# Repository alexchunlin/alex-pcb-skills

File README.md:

# alex-pcb-skills

**Pilot release: [v0.1.0-rc.1](docs/releases/v0.1.0-rc.1.md).** The completed tool changes are consolidated for
reviewed pilot-board trials. No board from this design loop has been manufactured and validated yet.

**Claude designs KiCad boards from code, routes them with a deterministic router, checks them the way an electrical
reviewer would, and packages them for the fab. Every rule in the skills points at a measured finding.**

<p align="center"><sub>A brushed-DC motor channel (DRV8874 H-bridge, TPS54620 buck, AMS1117 LDO, encoder port, 2x5 control
header, 4 layers, 50 x 40 mm), designed from a one-page brief by Claude Opus 5.5 in 71 minutes, routed by
<code>pcb route auto</code>, scored 8 / 8 / 7 by an independent reviewer agent. Nothing in it was drawn by hand.</sub></p>

## Why

An engineer's week on a board goes mostly to things a machine does better: checking every pin against the datasheet,
every rail against its current, every cap against its distance, every claim in the design log against the file. Agents
write schematics as code well (the netlist has been right on every attempt so far) and they fail in the same places every
time: a 3 A rail reaching a header pin through four 0.3 mm thermal spokes, a bulk cap fed through a chain of single vias,
a 2x10 part bought for a 2x5 footprint, a board setting lowered until DRC reads zero. ERC and DRC are blind to all of
these. `pcbcheck` turns the brief into rows that fail on them, `pcb q` measures the board so the designer and the reviewer
argue over numbers, and the reviewer's new majors become rows within a day.

Same briefs, scored by an independent reviewer agent on electrical correctness, manufacturability and documentation:

| | Rung 1, Qwiic IMU breakout | Rung 2, motor channel |
|---|---|---|
| Without the tools | 9 / 8 / 8 in 48.7 min (best of two) | not attempted |
| With the designer skill | **9 / 9 / 8 in 42.9 min** | 8 / 6 / 7 in 38.7 min (best of three) |
| With the skill and `pcb route auto` | | **8 / 8 / 7 in 71.3 min** |

The time went where the evidence said it would: three designers lost most of a rung-2 run at the DRV8874's 0.65 mm pitch,
so the next tool was a router. It routes the finished boards clean in under a minute with half the designers' vias. The
score moved; the time did not yet, because the router was allowed to make choices that are rules. That is the next item
in [`docs/ROADMAP-2026-11-01.md`](docs/ROADMAP-2026-11-01.md).

## What a run looks like

1. **Code is the source of truth.** The designer writes Zener (or SKiDL) modules, one per subsystem. The KiCad schematic
   and board are generated, and `pcb regen-check` proves the hand-placed copper survives a regeneration from a clean tree.
2. **Placement and pours by script**, with `pcblib.board` over pcbnew. Net classes, planes and keepouts come from
   `checks.json`, the declared intent: rails, currents, buses, pin maps, test points.
3. **Routing by tool.** `pcb route auto` wraps KiCadRoutingTools: engine pass, refill, dual DRC, a second pass on what is
   still open, a stitch pass. Clean means zero airwires and no new errors; the router's own "all routed" is never the
   verdict.
4. **Checks that read the brief.** `pcb check` runs the intent rows; `pcb drc` runs KiCad's DRC twice, plain and with the
   fab's rule pack, and refuses a board setup lowered below the policy.
5. **Fab package and bring-up.** Gerbers, drill, JLC BOM and CPL with sourcing fields on every part, renders, a numbered
   `BRINGUP.md` with expected readings.
6. **Independent review.** A second agent re-runs everything on a copy, re-measures every claim with `pcb q`, and scores
   against anchors. Its findings are labelled on the archived board and replayed against every tool commit.

<p align="center"><sub>The attempt-2 board with the designer's copper stripped and placement kept, then <code>pcb route auto</code>:
61 airwires to 0 in 39.5 s, 43 vias against the designer's 64. The verdict is NOT CLEAN because one thermal relief is
starved, and that one error is what the designer gets back. Pours are hidden in this view.</sub></p>

## What it catches

| Rows | Catch |
|---|---|
| `feeds`, `currents` | A pin on a wide net fed through a via, a pour neck or plane spokes below the declared current (IPC-2221, barrel plating included); a 0.2 mm track on a 3 A net |
| `decoupling`, `thermal_vias` | A bypass cap farther from its pin than the datasheet asks, on any pin type; too few vias under a thermal pad |
| `policy`, `fields` | Clearance, track, via and silk minimums lowered below the brief; parts without MPN, Manufacturer, LCSC and Datasheet |
| `calcs` | Pull-up current, buck ripple, LDO dissipation, sense scaling, each a formula with a limit that reads values from the netlist |
| pin maps, connectors, jumpers, test points | The control header against the firmware table, Qwiic pin order, address jumpers, every test point in the bring-up doc |
| dual DRC, `regen-check` | Errors that only show with the fab pack loaded; copper that does not survive regeneration |

Every row cites the finding that motivated it in [`docs/FINDINGS.md`](docs/FINDINGS.md). The replay bench
(`tools/bench/`) holds 10 boards and 41 labelled findings, including MotorGo Plink's real fab bugs; a tool commit has to
raise recall without adding a false fail. `tools/verify_all.sh` runs the integration and regression checks; see the release notes for the current validation result and prerequisites.

<p align="center"><sub>Rung 1, a Qwiic LSM6DS3TR-C breakout (Sonnet 5.5 with the skill, 9 / 9 / 8), and rung 2, the motor channel
(Opus 5.5 with the skill and the router, 8 / 8 / 7). Both are in <code>examples/</code> with their configs, reviews and labels.</sub></p>

## Where it is

- The sensor breakout received reviewer scores of 9 on electrical with minors only; it has not been physically validated. The
  named risk for a new part is sourcing: the one blocker in rung 2 was an LCSC part that did not match its footprint,
  and the row for that is next.
- The motor channel works on paper and would be a rev A with errata: the reviewer's three majors are a header pin on
  plane spokes, a bulk cap on a via chain, and no copper under the LDO. All three are labelled and all three are the
  router's choices, which the staged router removes.
- Nothing from the loop has been built yet. Every score is reviewer-measured. Ordering the two best boards is the
  cheapest calibration available and is spike [#3](https://github.com/alexchunlin/alex-pcb-skills/issues/3).

## Where it is going

- **Staged routing** that keeps signals off the planes and wide nets with the layout script, generated `feeds` rows for
  every pin of a wide net, and the datasheet rules moved from the model's thinking into `pcblib` helpers. Then rung-2
  attempt 3, with the target of 8 / 8 / 7 or better under 40 minutes.
- **Rung 3**: re-derive the MotorGo Plink (four channels, ESP32, IMU, USB) from a brief written from its README, with one
  sub-agent per schematic sheet. **Rung 4**: Pace Racer's 48 V inverter sheet.
- **Five spikes, run and merged** (`docs/spikes/`, issues #1 to #5), each with a hypothesis, a null, a cost, a
  literature review and an Opus agent that ran it in a worktree. What paid: a field solve of the declared currents on
  the real copper that passes a pour-fed board where the track-width row fails every pad and found a 3 A via pair nobody
  had labelled (#3); a mutation bench that plants six bug kinds and shows the boards' own checks catch 16 of 21, with
  every miss a missing config row (#3); a placement prior mined from 72 public boards that doubles the router's clean
  rate, 33 of 50 against 17 of 50 (#2); a generated pogo jig and bring-up script waiting on a board order (#3). What
  lost, by a number: a learned placement surrogate against plain wirelength (#1), agent-drawn routing corridors (#4),
  reference-circuit statistics and commit mining (#2). Pooling that prior by component class gives a new part one:
  39 of 50 with the part held out, against 17 uniform, though KRT's own decap cost ties it at 37 (#5).
- **A robot design acceleration toolkit.** This repo, [`alex-3d-skills`](https://github.com/alexchunlin/alex-3d-skills)
  (printed assemblies checked in headless Blender) and Harnessy (wire harnesses with design rules and a BOM) are three
  views of one machine: the board's connectors are the harness's endpoints, the harness's lengths come from the
  assembly, and the assembly's mounting holes and keepouts come from the board. The plan is one brief in, a checked
  board, harness and enclosure out, with the same loop, the same review protocol and the same replay bench behind each.

## Layout of the repo

| Path | What |
|---|---|
| `skills/kicad-design/` | Designer skill: the `pcb` wrapper (`erc`, dual `drc`, `check`, `q`, `route`, `fab`, `regen-check`, `schfix`, `py`, Diode passthrough), `pcblib.board` over pcbnew, `pcbcheck` with `checks.json`, reference docs, project template |
| `skills/pcb-design-review/` | Reviewer skill: check-first protocol, rubric with anchors, evidence checklist |
| `examples/` | The reviewed rung-1 and rung-2 attempts (configs, boards, reviews, labels) and MotorGo Plink before and after its rework |
| `tools/verify_all.sh` | Re-proves everything (`--changed [BASE]` runs only what a change affects, `--dry-run` prints the plan) |
| `tools/bench/` | Replay bench (`replay.py`, `labels.json`) and the route bench (`route_bench.py`, `results/route.jsonl`) |
| `tools/readme/` | `make_images.sh` rebuilds the images above from the archived boards |
| `bench/design/` | Design-bench briefs (rung 1 Qwiic IMU, rung 2 motor channel) and the review protocol |
| `docs/` | `GAMEPLAN.md`, `ROADMAP-2026-11-01.md`, `FINDINGS.md` (the evidence log), `STATUS.md`, `SURVEY-2026-10-31.md`, session handoffs, upstream issue drafts |

## Requirements

KiCad 10.0.1 at `/Applications/KiCad/KiCad.app` (kicad-cli and the bundled Python with `pcbnew`), Diode `pcb` 0.4.97
at `~/.local/bin/pcb` for the Zener front end, kicad-druid at `/tmp/pcb-ref/kicad-druid` (`KICAD_DRUID`) for the fab
rule packs, python3. No pip dependencies for the tools; `.venv` holds SKiDL for the fallback path. `pcb route auto` needs
KiCadRoutingTools under `/tmp/pcb-ref/` (the six-line install is in `tools/bench/README.md`). Only tested on macOS.

## Install

```sh
git clone https://github.com/alexchunlin/alex-pcb-skills.git && cd alex-pcb-skills
git checkout v0.1.0-rc.1
mkdir -p ~/.claude/skills
ln -s "$PWD/skills/kicad-design" ~/.claude/skills/kicad-design              # the designer skill
ln -s "$PWD/skills/pcb-design-review" ~/.claude/skills/pcb-design-review    # the reviewer skill
```

## Quick use

```sh
S=~/code-stuff/alex-pcb-skills/skills/kicad-design/scripts
$S/pcb drc layout/x/x.kicad_pcb --pack jlcpcb        # plain and packed DRC, sentinel, pack floored to the board setup
$S/pcb check layout/x/x.kicad_pcb checks.json        # intent rows; undeclared rails, connectors, jumpers, test points fail
$S/pcb q layout/x/x.kicad_pcb decoupling             # one measurement (pcb q alone lists them)
$S/pcb route auto layout/x/x.kicad_pcb --pack jlcpcb # route what is unrouted, dual DRC, exit 1 unless clean
$S/pcb fab layout/x/x.kicad_pcb --out fab            # gerbers, drill, JLC BOM and CPL, renders, fab.json
$S/pcb regen-check . --cmd tools/regen.sh --board layout/x/x.kicad_pcb --generated layout fab
$S/pcb schfix layout/x/x.kicad_sch                   # after pcb apply schematic
$S/pcb py tools/layout_board.py layout/x/x.kicad_pcb # a pcblib layout script
sh tools/verify_all.sh --changed --dry-run           # what this change affects
python3 -I tools/bench/replay.py                     # the replay bench on HEAD
```

Then give Claude Code a brief like `bench/design/rung2-motor-channel/BRIEF.md` and ask for a board; ask a second session
to review it with the `pcb-design-review` skill.

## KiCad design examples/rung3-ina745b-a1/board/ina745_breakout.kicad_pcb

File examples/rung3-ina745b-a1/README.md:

# INA745B Power Monitor Breakout

Measures current, bus voltage, power, energy and charge on a rail up to 40 V, over I2C, with the shunt inside the chip. Bolt the rail to two M4 terminals, plug in Qwiic, read the numbers.
40 x 25.4 mm, four M2.5 holes. Open hardware, source in Zener and Python.

**Rated 25 A continuous at 40 C ambient in still air, 40 V.** That is this board's calculation, not the chip's 35 A headline; see DESIGN_LOG.md section 2. 33 mV drop at 25 A.
The rating is calculated, not yet measured on a built board.

| Spec | Value |
|---|---|
| Sensor | TI INA745B, 16-bit, 1.2 mA/LSB, 3.125 mV/LSB, full scale +/-39.32 A |
| Accuracy | gain +/-1.25 %, offset +/-62.5 mA max (B grade) |
| Bus | -0.1 to 40 V, high side or low side |
| Logic supply | VIN 3.3 to 5.5 V on the header, or 3.3 V on Qwiic |
| I2C | 0x40 default, 100 kHz; up to 2.94 MHz in the chip |

## Pinout
| Header J3 | Name | Function |
|---|---|---|
| 1 | VIN | 3.3 to 5.5 V in, through a diode and a 3.3 V regulator |
| 2 | 3V3 | Logic rail, same copper as Qwiic 3V3 |
| 3 | GND | Logic ground. **Must be common with the measured rail's return** |
| 4 | SCL | I2C clock |
| 5 | SDA | I2C data |
| 6 | ALERT | Open drain, active low, 10 k to 3V3. Do not pull above 3.6 V |

J1, J2: Qwiic / Stemma QT, 1 GND, 2 3V3, 3 SDA, 4 SCL. J4 IS+, J5 IS-: M4 screw terminals. TP1 GND, TP2 3V3, TP3 VBUS wire pad.

## I2C address
| JP4 (A1) | JP3 (A0) | Address |
|---|---|---|
| G | G | 0x40 (shipped) |
| G | V | 0x41 |
| V | G | 0x44 |
| V | V | 0x45 |
To move a strap, cut the link to G and bridge to V. Never leave a jumper open. A wire to SCL gives more addresses (TI table 6-2); SDA needs a 100 ns hold your host may not give.

## Jumpers
JP1: closed, VBUS senses IS+ (high side). Low side: cut it and wire your rail to TP3. JP2: cut both links to drop the 10 k pull-ups. JP5: cut to turn off the power LED.

## Wiring
High side: supply + to J4, load to J5, supply - to GND. Low side: load return to J4, J5 to supply -, cut JP1, supply + to TP3, GND to the same return as J5.
Use M4 ring lugs and 10 AWG (5 mm2) wire at 25 A. Keep logic ground connected whenever the board is powered (TI 8.3).
5 V hosts: SDA and SCL tolerate 5.5 V, but they idle at 3.3 V, so a host needing 3.5 V for a high needs a level shifter.
10 k pull-ups meet 400 kHz only to 35 pF. At 400 kHz, add a stronger host pull-up or run 100 kHz.

## First read
Register 0x3E reads 0x5449. BRINGUP.md has the full sequence with expected values.

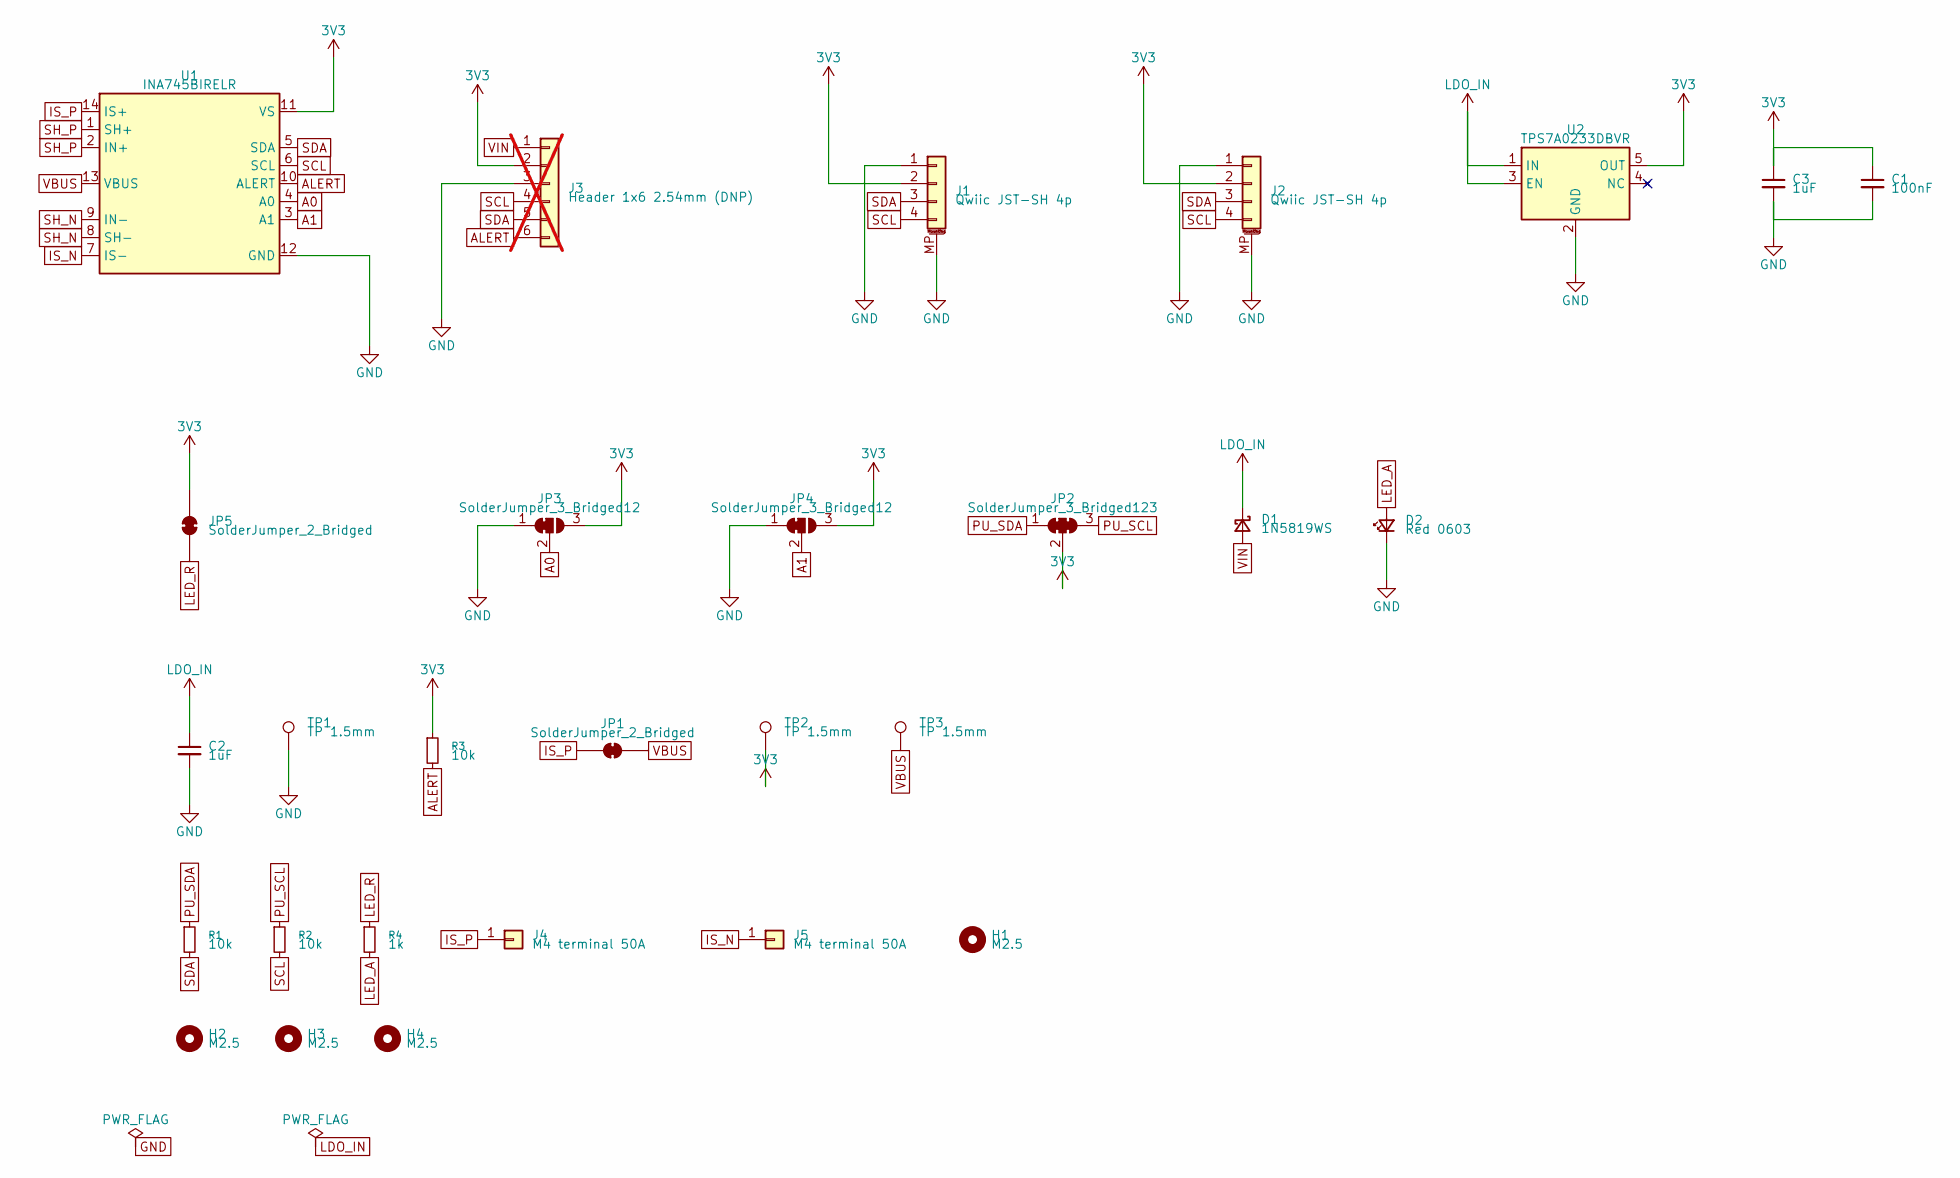
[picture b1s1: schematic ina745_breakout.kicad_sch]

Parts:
C1: 100nF; C_0402_1005Metric_NoSilk; MPN CL05B104KO5NNNC; LCSC C1525
C2, C3: 1uF; C_0603_1608Metric; MPN CL10A105KB8NNNC; LCSC C15849
D1: 1N5819WS; D_SOD-323; MPN 1N5819WS; LCSC C191023
D2: Red 0603; LED_0603_1608Metric; MPN KT-0603R; LCSC C2286
H1, H2, H3, H4: M2.5; MountingHole_2.7mm_M2.5_Head4.7
J1, J2: Qwiic JST-SH 4p; JST_SH_SM04B-SRSS-TB_1x04-1MP_P1.00mm_Horizontal; MPN SM04B-SRSS-TB(LF)(SN); LCSC C160404
J3: Header 1x6 2.54mm (DNP); PinHeader_1x06_P2.54mm_Vertical; MPN PZ254V-11-06P; LCSC C492405; not fitted
J4, J5: M4 terminal 50A; XFCN_T44008_M4; MPN T44008; LCSC C481445
JP1: SolderJumper_2_Bridged; SolderJumper-2_P1.6mm_Bridged12_Pad1.0x1.5mm
JP2: SolderJumper_3_Bridged123; SolderJumper-3_P1.3mm_Bridged123_Pad1.0x1.5mm
JP3, JP4: SolderJumper_3_Bridged12; SolderJumper-3_P1.3mm_Bridged12_Pad1.0x1.5mm
JP5: SolderJumper_2_Bridged; SolderJumper-2_P1.3mm_Bridged12_Pad1.0x1.5mm
R1, R2, R3: 10k; R_0603_1608Metric; MPN 0603WAF1002T5E; LCSC C25804
R4: 1k; R_0603_1608Metric; MPN 0603WAF1001T5E; LCSC C21190
TP1, TP2: TP 1.5mm; TestPoint_Pad_D1.5mm_Ring1.0
TP3: TP 1.5mm; TestPoint_THTPad_D2.0mm_Drill1.0mm
U1: INA745BIRELR; VQFN-14_REL0014A_3x5mm_P0.6mm; MPN INA745BIRELR; LCSC C35213810
U2: TPS7A0233DBVR; SOT-23-5; MPN TPS7A0233DBVR; LCSC C5142805

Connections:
3V3: C1.1, C3.1, J1.2, J2.2, J3.2, JP2.2 (C), JP3.3 (B), JP4.3 (B), JP5.1 (A), R3.1, TP2.1, U1.11 (VS), U2.5 (OUT)
A0: JP3.2 (C), U1.4 (A0)
A1: JP4.2 (C), U1.3 (A1)
ALERT: J3.6, R3.2, U1.10 (ALERT)
GND: C1.2, C2.2, C3.2, D2.1 (K), J1.1, J1.MP (MountPin), J2.1, J2.MP (MountPin), J3.3, JP3.1 (A), JP4.1 (A), TP1.1, U1.12 (GND), U2.2 (GND)
IS_N: J5.1, U1.7 (IS-)
IS_P: J4.1, JP1.1 (A), U1.14 (IS+)
LDO_IN: C2.1, D1.1 (K), U2.1 (IN), U2.3 (EN)
LED_A: D2.2 (A), R4.2
LED_R: JP5.2 (B), R4.1
PU_SCL: JP2.3 (B), R2.1
PU_SDA: JP2.1 (A), R1.1
SCL: J1.4, J2.4, J3.4, R2.2, U1.6 (SCL)
SDA: J1.3, J2.3, J3.5, R1.2, U1.5 (SDA)
SH_N: U1.8 (SH-), U1.9 (IN-)
SH_P: U1.1 (SH+), U1.2 (IN+)
VBUS: JP1.2 (B), TP3.1, U1.13 (VBUS)
VIN: D1.2 (A), J3.1
power.U2.NC_U_NC: U2.4 (NC)

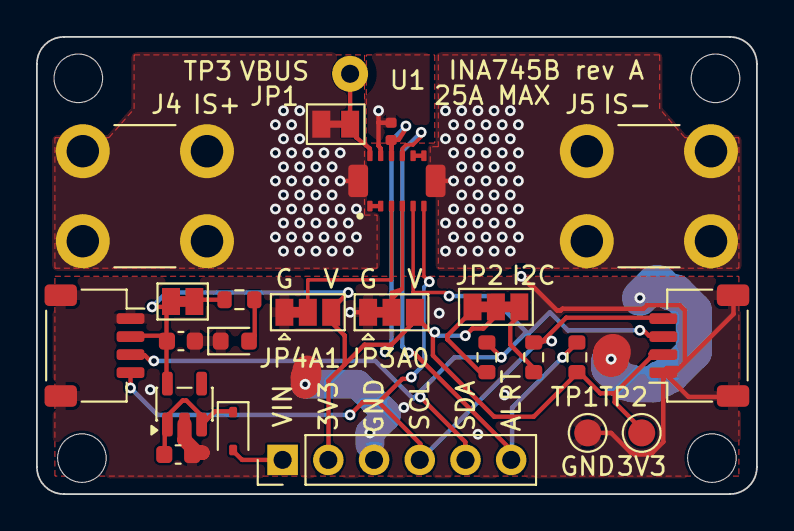
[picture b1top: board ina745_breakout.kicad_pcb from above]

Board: 4 copper layers, 40.0 x 25.4 mm, 28 parts (0 on the bottom side), 18 nets.

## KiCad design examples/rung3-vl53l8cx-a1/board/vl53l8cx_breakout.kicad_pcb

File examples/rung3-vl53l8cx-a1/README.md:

# VL53L8CX 8 x 8 Time-of-Flight Breakout, Qwiic

64-zone distance sensing to 4 m with a 45 x 45 degree field of view, up to 60 Hz. Plug into any 3.3 V Qwiic / STEMMA QT host. The ST VL53L8CX runs on 1.8 V logic and three supplies; this board makes the 1.8 V, sequences it the way the datasheet asks, and level-shifts all eight signal lines.

25.4 x 17.8 mm, two M2.5 holes, 4 layers, open hardware.

## Pinout: J3, 0.1 inch

| Pin | Name | Dir | Function |
|---|---|---|---|
| 1 | VIN | in | 3.3 to 5 V, to the on-board 3.3 V regulator |
| 2 | 3V3 | in/out | sensor rail, same net as Qwiic 3V3, 170 mA max load from this board |
| 3 | GND | | |
| 4 | MISO | out | SPI only, after bridging JP5 |
| 5 | SCL | in | I2C clock, SPI MCLK. 3.3 V level |
| 6 | SDA | in/out | I2C data, SPI MOSI. 3.3 V level |
| 7 | NCS | in | SPI chip select |
| 8 | RST | in | high pulse resets the I2C interface only. Leave open if unused. Full sensor reset is a power cycle (DS14161 Table 3 note) |
| 9 | LPN | in | low disables I2C in low-power mode. Open = enabled |
| 10 | INT | out | open-drain interrupt with a 10k pull-up to 3.3 V |

All logic on J3 and Qwiic is 3.3 V. Inputs tolerate 5 V, but a 5 V host will read SDA and INT high at only 3.3 V, so use a 3.3 V host. VIN is the only pin meant for 5 V. SYNC is on back pad TP4, 3.3 V side, with no pull-up on that side.

Qwiic J1 and J2: 1 GND, 2 3V3, 3 SDA, 4 SCL.

## I2C address

**0x29** (7-bit), 0x52 in ST's 8-bit notation. No strap: change it in software, using LPN to keep other sensors quiet. Host-side pull-ups are 10k, through JP1 on the top by J2: cut it once to remove both on a long chain. This board guarantees 400 kHz with 10k; 1 MHz needs stronger host pull-ups.

## Power

Two sources share the 3V3 rail: Qwiic 3V3, and VIN through the regulator and an ideal diode. Either or both are fine. VIN cannot be back-fed from Qwiic. With VIN on, this board powers the Qwiic connectors, so a host that is switched off on the same cable gets power on its 3V3 rail: disconnect it. The LED shows the rail; cut JP2 on the back to turn it off. Typical sensor power 215 mW while ranging.

## Cover glass

The board ships with ST's protective liner on the sensor: **peel it off before use**. If you put the board behind a window, the opening must be at least as wide as the 57.9 x 57.9 degree collector cones (DS14161 sect 2.2, Fig 28), and the glass affects crosstalk: see ST AN5897. The exclusion zone is on layer `User.1` of the KiCad board.

## I2C to SPI

Move JP3 and JP4 to pads 2-3, bridge JP5, power cycle. `BRINGUP.md` has the steps.

## Software

ST's VL53L8CX ULD driver (STSW-IMG040); user manual UM3109. Rev A has not been built or tested.

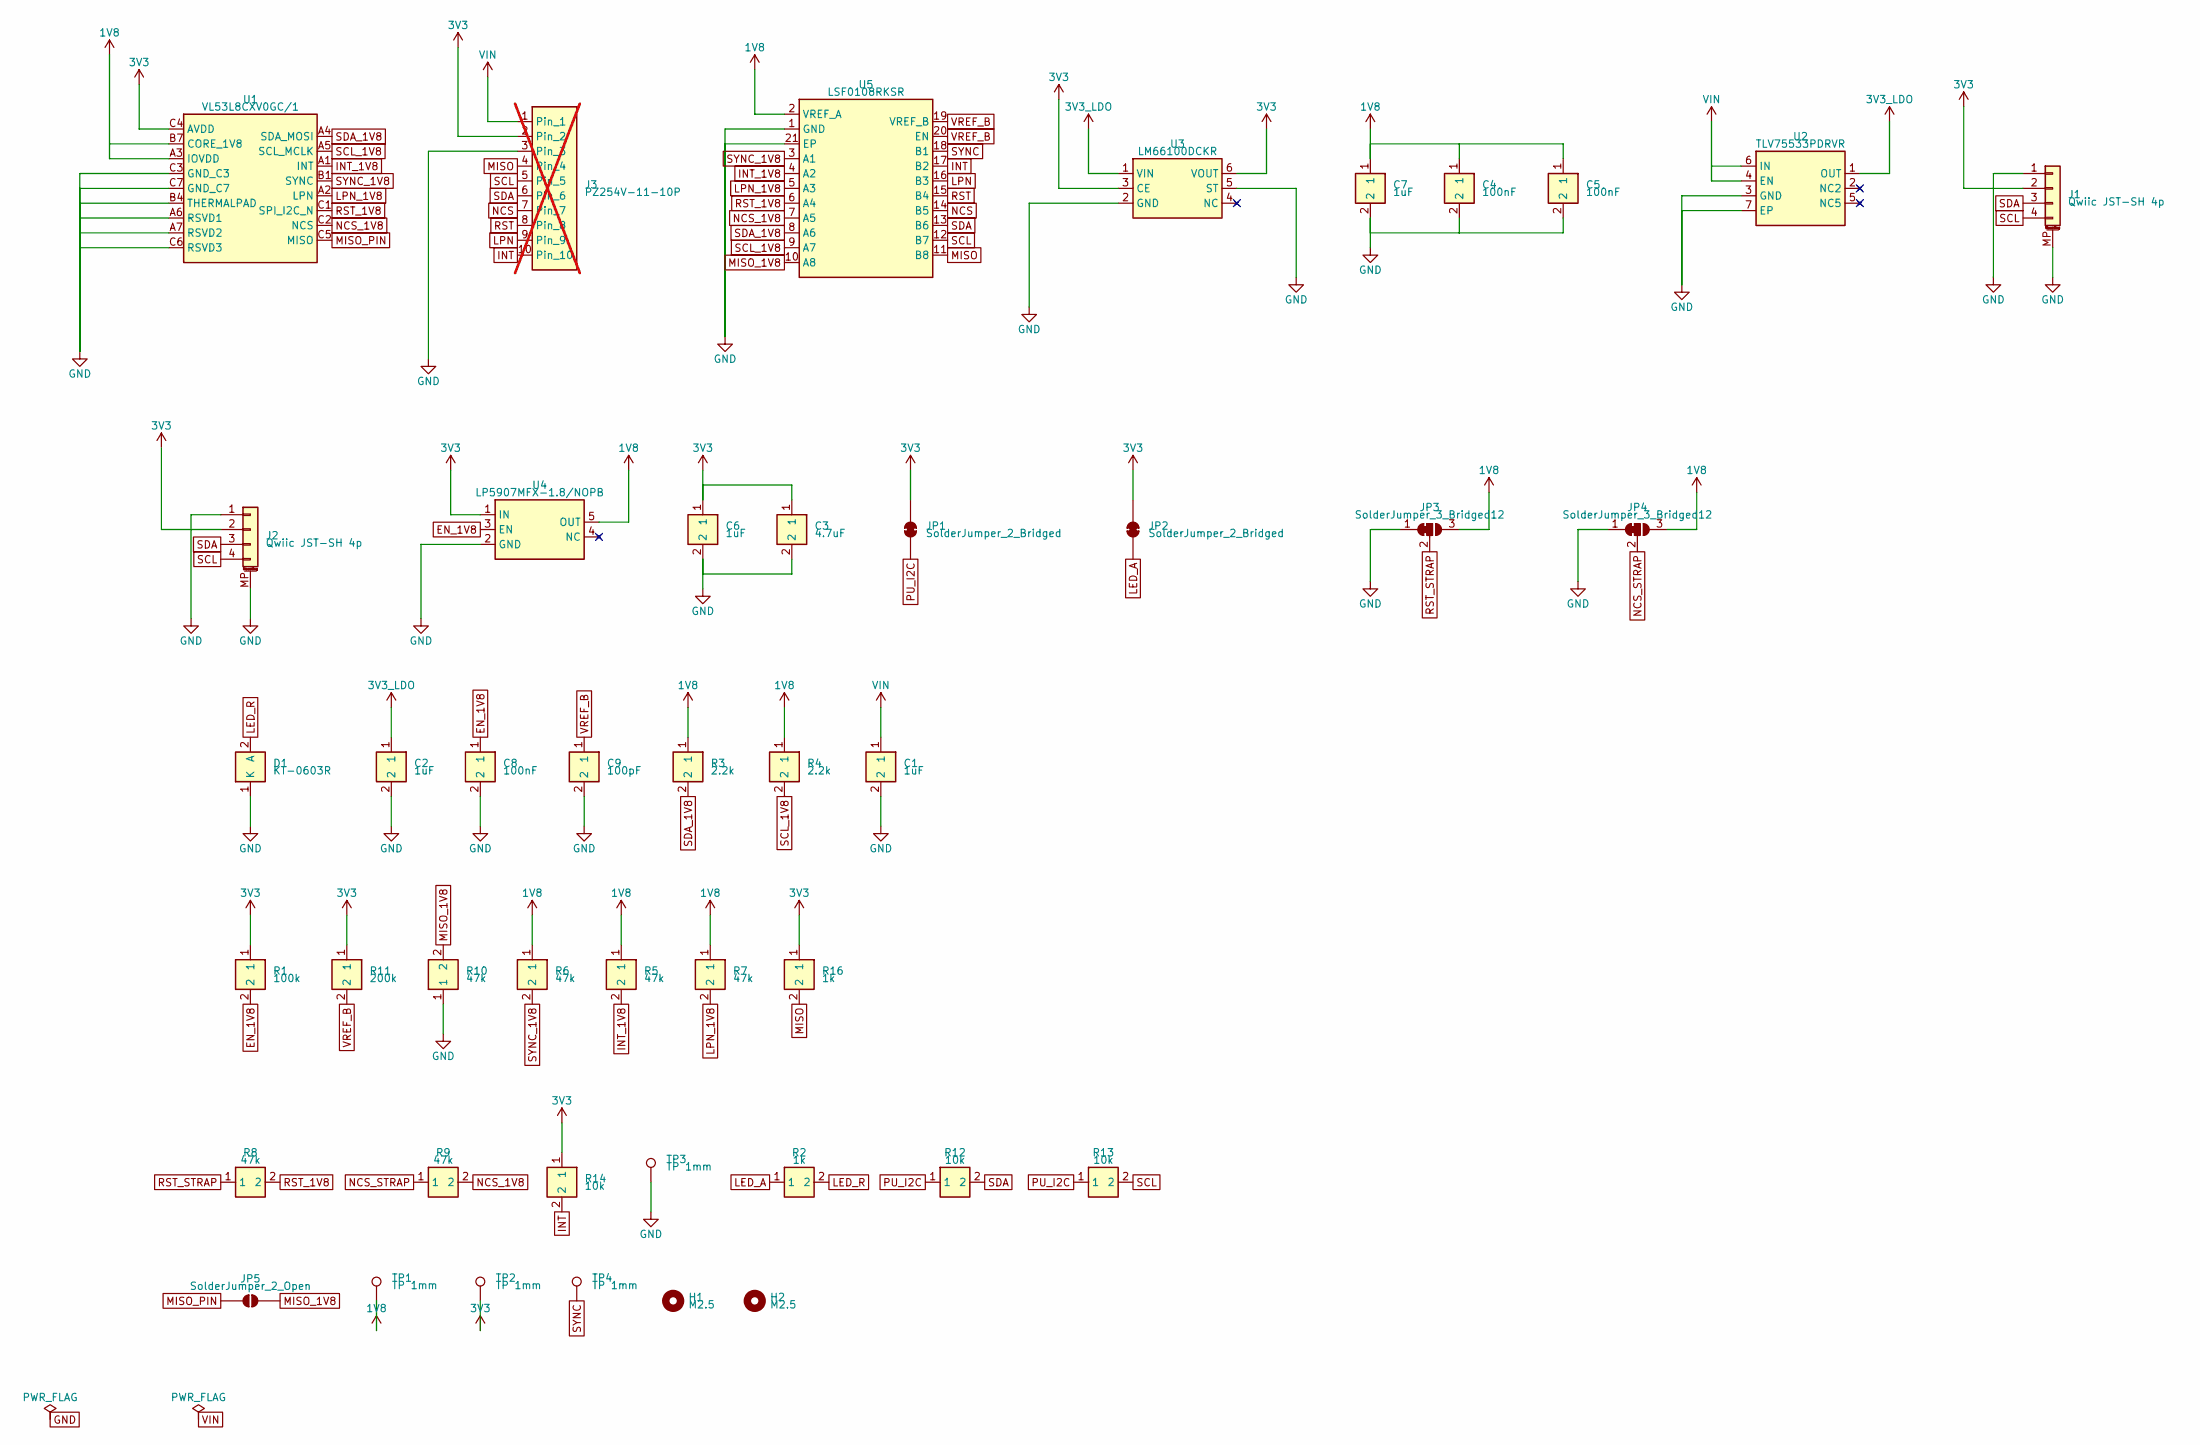
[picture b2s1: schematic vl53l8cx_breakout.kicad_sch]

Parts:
C1, C2, C6, C7: 1uF; C_0402_1005Metric; MPN CL05A105KA5NQNC; LCSC C52923
C3: 4.7uF; C_0603_1608Metric; MPN CL10A475KO8NNNC; LCSC C19666
C4, C5, C8: 100nF; C_0402_1005Metric; MPN CL05B104KO5NNNC; LCSC C1525
C9: 100pF; C_0402_1005Metric; MPN 0402CG101J500NT; LCSC C1546
D1: KT-0603R; LED_0603_1608Metric; MPN KT-0603R; LCSC C2286
H1, H2: M2.5; MountingHole_2.7mm_M2.5
J1, J2: Qwiic JST-SH 4p; JST_SH_SM04B-SRSS-TB_1x04-1MP_P1.00mm_Horizontal; MPN SM04B-SRSS-TB(LF)(SN); LCSC C160404
J3: PZ254V-11-10P; PinHeader_1x10_P2.54mm_Vertical; MPN PZ254V-11-10P; LCSC C492409; not fitted
JP1, JP2: SolderJumper_2_Bridged; SolderJumper-2_P1.3mm_Bridged12_Pad1.0x1.5mm
JP3, JP4: SolderJumper_3_Bridged12; SolderJumper-3_P1.3mm_Bridged12_Pad1.0x1.5mm
JP5: SolderJumper_2_Open; SolderJumper-2_P1.3mm_Open_Pad1.0x1.5mm
R1: 100k; R_0402_1005Metric; MPN 0402WGF1003TCE; LCSC C25741
R2, R16: 1k; R_0402_1005Metric; MPN 0402WGF1001TCE; LCSC C11702
R3, R4: 2.2k; R_0402_1005Metric; MPN 0402WGF2201TCE; LCSC C25879
R5, R6, R7, R8, R9, R10: 47k; R_0402_1005Metric; MPN 0402WGF4702TCE; LCSC C25792
R11: 200k; R_0402_1005Metric; MPN 0402WGF2003TCE; LCSC C25764
R12, R13, R14: 10k; R_0402_1005Metric; MPN 0402WGF1002TCE; LCSC C25744
TP1, TP2, TP3, TP4: TP 1mm; TestPoint_Pad_D1.0mm
U1: VL53L8CXV0GC/1; ST_VL53L8CX_LGA16; MPN VL53L8CXV0GC/1; LCSC C7386355
U2: TLV75533PDRVR; DFN-6-1EP_2x2mm_P0.65mm_EP1x1.6mm; MPN TLV75533PDRVR; LCSC C2861750
U3: LM66100DCKR; SOT-363_SC-70-6; MPN LM66100DCKR; LCSC C2869734
U4: LP5907MFX-1.8/NOPB; SOT-23-5; MPN LP5907MFX-1.8/NOPB; LCSC C92498
U5: LSF0108RKSR; DHVQFN-20-1EP_2.5x4.5mm_P0.5mm_EP1x3mm; MPN LSF0108RKSR; LCSC C130008

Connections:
1V8: C4.1, C5.1, C7.1, JP3.3 (B), JP4.3 (B), R3.1, R4.1, R5.1, R6.1, R7.1, TP1.1, U1.A3 (IOVDD), U1.B7 (CORE_1V8), U4.5 (OUT), U5.2 (VREF_A)
3V3: C3.1, C6.1, J1.2, J2.2, J3.2, JP1.2 (B), JP2.1 (A), R1.1, R11.1, R14.1, R16.1, TP2.1, U1.C4 (AVDD), U3.3 (CE), U3.6 (VOUT), U4.1 (IN)
3V3_LDO: C2.1, U2.1 (OUT), U3.1 (VIN)
EN_1V8: C8.1, R1.2, U4.3 (EN)
GND: C1.2, C2.2, C3.2, C4.2, C5.2, C6.2, C7.2, C8.2, C9.2, D1.1 (K), J1.1, J1.MP (MountPin), J2.1, J2.MP (MountPin), J3.3, JP3.1 (A), JP4.1 (A), R10.1, TP3.1, U1.A6 (RSVD1), U1.A7 (RSVD2), U1.B4 (THERMALPAD), U1.C3 (GND_C3), U1.C6 (RSVD3), U1.C7 (GND_C7), U2.3 (GND), U2.7 (EP), U3.2 (GND), U3.5 (ST), U4.2 (GND), U5.1 (GND), U5.21 (EP)
INT: J3.10, R14.2, U5.17 (B2)
INT_1V8: R5.2, U1.A1 (INT), U5.4 (A2)
LED_A: JP2.2 (B), R2.1
LED_R: D1.2 (A), R2.2
LPN: J3.9, U5.16 (B3)
LPN_1V8: R7.2, U1.A2 (LPN), U5.5 (A3)
MISO: J3.4, R16.2, U5.11 (B8)
MISO_1V8: JP5.2 (B), R10.2, U5.10 (A8)
MISO_PIN: JP5.1 (A), U1.C5 (MISO)
NCS: J3.7, U5.14 (B5)
NCS_1V8: R9.2, U1.C2 (NCS), U5.7 (A5)
NCS_STRAP: JP4.2 (C), R9.1
POWER.U2.NC_U_NC2: U2.2 (NC2)
POWER.U2.NC_U_NC5: U2.5 (NC5)
POWER.U3.NC_U_NC: U3.4 (NC)
POWER.U4.NC_U_NC: U4.4 (NC)
PU_I2C: JP1.1 (A), R12.1, R13.1
RST: J3.8, U5.15 (B4)
RST_1V8: R8.2, U1.C1 (SPI_I2C_N), U5.6 (A4)
RST_STRAP: JP3.2 (C), R8.1
SCL: J1.4, J2.4, J3.5, R13.2, U5.12 (B7)
SCL_1V8: R4.2, U1.A5 (SCL_MCLK), U5.9 (A7)
SDA: J1.3, J2.3, J3.6, R12.2, U5.13 (B6)
SDA_1V8: R3.2, U1.A4 (SDA_MOSI), U5.8 (A6)
SYNC: TP4.1, U5.18 (B1)
SYNC_1V8: R6.2, U1.B1 (SYNC), U5.3 (A1)
VIN: C1.1, J3.1, U2.4 (EN), U2.6 (IN)
VREF_B: C9.1, R11.2, U5.19 (VREF_B), U5.20 (EN)

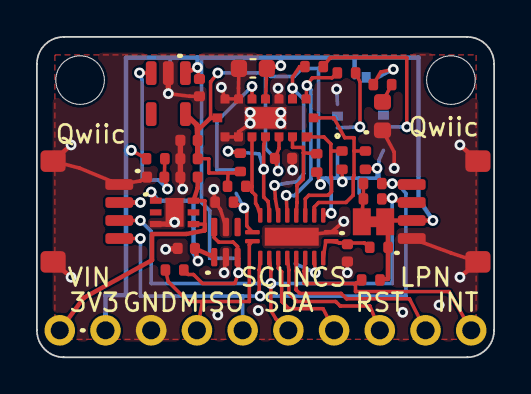
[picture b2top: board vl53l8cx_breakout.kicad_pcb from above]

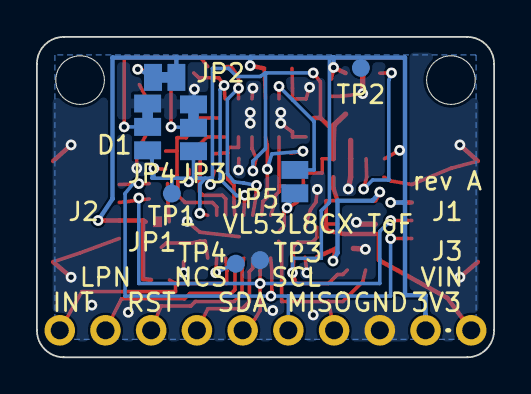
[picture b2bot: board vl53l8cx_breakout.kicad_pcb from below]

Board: 4 copper layers, 25.4 x 17.8 mm, 44 parts (8 on the bottom side), 29 nets.

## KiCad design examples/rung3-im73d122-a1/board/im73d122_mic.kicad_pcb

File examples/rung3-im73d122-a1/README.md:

# IM73D122 PDM Microphone Breakout

A 73 dB(A) SNR digital MEMS microphone on a 25.4 x 17.8 mm board, for far-field pickup. Infineon IM73D122V01: PDM output, 122 dBSPL acoustic overload, flat 20 Hz to 19 kHz, IP57 at the component. The sound port is a 0.8 mm hole through the board: sound enters from the **back**. On-board TPS7A2033 low-noise 3.3 V regulator (7 to 10 uVrms) so a noisy 5 V USB rail does not reach the mic. Two boards on one CLK and DATA make a stereo pair.

There is no I2C and no address. Data is 1-bit PDM; your host needs a PDM input (RP2040 PIO, nRF52840, ESP32-S3, STM32 with DFSDM or SAI).

## Pinout (J1, 0.1 in, left to right on the top view)

| Pin | Name | Dir | What it does |
|---|---|---|---|
| 1 | VIN | in | 3.3 to 5.5 V. Above 3.6 V the regulator has headroom and its noise rejection works |
| 2 | 3V3 | out | Regulated 3.3 V, 5 mA at most. With JP3 cut: input, 1.62 to 3.6 V direct |
| 3 | GND | | Ground |
| 4 | DATA | out | PDM data, 100 ohm series. Tri-state on the other channel's edge |
| 5 | CLK | in | PDM clock. 3.3 V logic, not 5 V tolerant. See table |
| 6 | SEL | in | L/R select. Tied low by JP2 as shipped |

| CLK | Mode | SNR | Current |
|---|---|---|---|
| 0.768 MHz | Low power | 69 dB(A) | 0.28 mA |
| 1.536 MHz | Normal | 71 dB(A) | 0.69 mA |
| 2.4 MHz | High perf | 72 dB(A) | 0.75 mA |
| 3.072 MHz | High perf | 73 dB(A) | 0.98 mA |
| 4.8 MHz | Ultrasonic | 72 dB(A) | 0.90 mA |

Clock duty 40 to 60 % up to 3 MHz, 48 to 52 % above. Clock edges 13 ns or faster.

## Jumpers

| Jumper | Shipped | Change it to |
|---|---|---|
| JP1 LED | bridged | Cut: power LED off, saves 1.3 mA |
| JP2 L/R | L (SEL low, DATA driven on the falling edge) | Cut, bridge R: SEL to 3V3, second channel, DC offset -40 instead of -80 dBFS. Cut only: drive SEL from a host |
| JP3 LDO | bridged | Cut: regulator disconnected, feed 3V3 directly at 1.62 to 3.6 V. Do this for a 1.8 V host |

**Power, one source at a time.** Shipped: VIN feeds the LDO, 3V3 is an output. With JP3 bridged never drive 3V3 from outside: the TPS7A20 must not see OUT above IN + 0.3 V. Cut JP3 first.

**Mounting.** Four M2.5 holes. Keep the back of the port open: pins down on a breadboard, the header's 2.5 mm plastic spacer is all the gap the port gets, so solder the header pins up, or expect the board to hear the breadboard. If you solder wires, do not pot or conformal-coat near the port. Use no-clean flux, do not wash, do not blow air into the hole, never ultrasonic clean.

Files: `fab/` Gerbers (`im73d122_mic_gerbers_order.zip`), JLC BOM and CPL; `BRINGUP.md`; `DESIGN_LOG.md`.

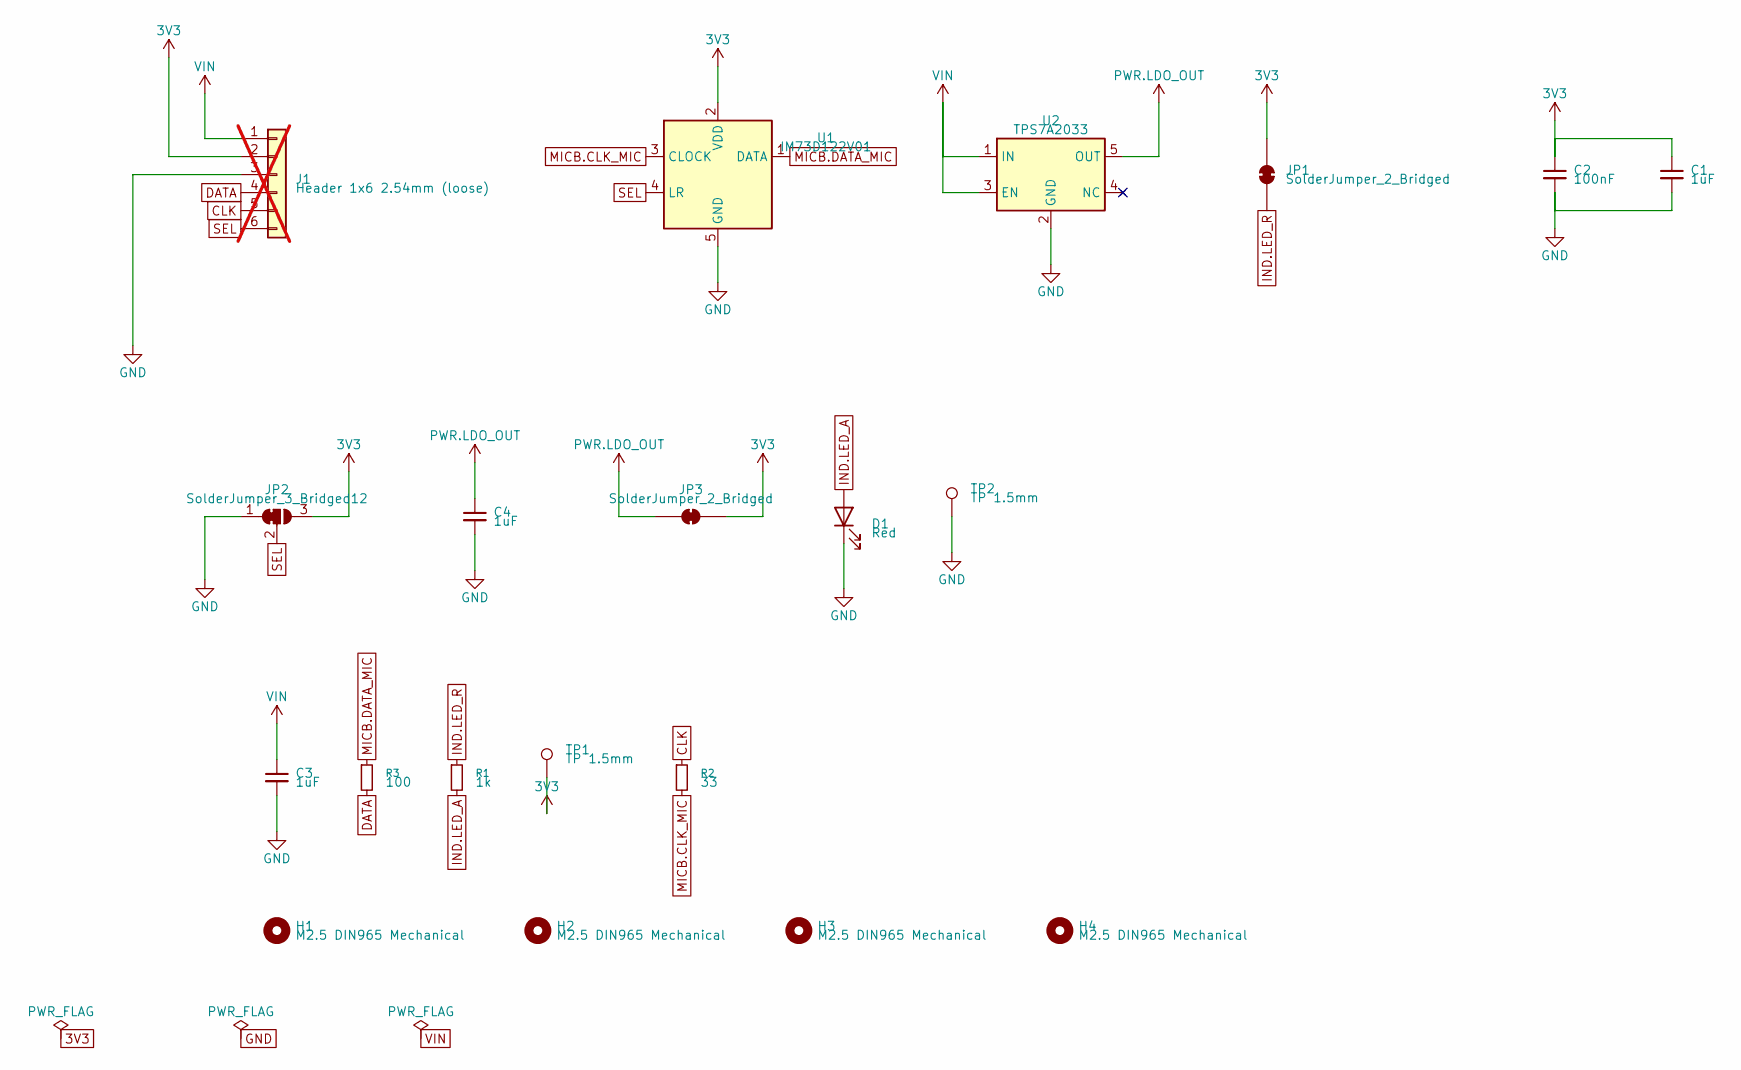
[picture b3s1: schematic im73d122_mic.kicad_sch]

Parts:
C1, C3, C4: 1uF; C_0402_1005Metric; MPN CL05A105KA5NQNC; LCSC C52923
C2: 100nF; C_0402_1005Metric; MPN CL05B104KO5NNNC; LCSC C1525
D1: Red; LED_0603_1608Metric; MPN KT-0603R; LCSC C2286
H1, H2, H3, H4: M2.5 DIN965 Mechanical; MountingHole_2.7mm_M2.5_DIN965
J1: Header 1x6 2.54mm (loose); PinHeader_1x06_P2.54mm_Vertical; MPN HX PZ2.54-1x6P ZZ; LCSC C32713272; not fitted
JP1, JP3: SolderJumper_2_Bridged; SolderJumper-2_P1.3mm_Bridged12_Pad1.0x1.5mm
JP2: SolderJumper_3_Bridged12; SolderJumper-3_P1.3mm_Bridged12_Pad1.0x1.5mm
R1: 1k; R_0402_1005Metric; MPN 0402WGF1001TCE; LCSC C11702
R2: 33; R_0402_1005Metric; MPN 0402WGF330JTCE; LCSC C25105
R3: 100; R_0402_1005Metric; MPN 0402WGF1000TCE; LCSC C25076
TP1, TP2: TP 1.5mm; TestPoint_Pad_D1.5mm
U1: IM73D122V01; IM73D122V01_LLGA-5; MPN IM73D122V01XTMA1; LCSC C5563886
U2: TPS7A2033; SOT-23-5; MPN TPS7A2033PDBVR; LCSC C2862740

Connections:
3V3: C1.1, C2.1, J1.2, JP1.1 (A), JP2.3 (B), JP3.2 (B), TP1.1, U1.2 (VDD)
CLK: J1.5, R2.1
DATA: J1.4, R3.2
GND: C1.2, C2.2, C3.2, C4.2, D1.1 (K), J1.3, JP2.1 (A), TP2.1, U1.5 (GND), U2.2 (GND)
IND.LED_A: D1.2 (A), R1.2
IND.LED_R: JP1.2 (B), R1.1
MICB.CLK_MIC: R2.2, U1.3 (CLOCK)
MICB.DATA_MIC: R3.1, U1.1 (DATA)
PWR.LDO.NC_U_NC: U2.4 (NC)
PWR.LDO_OUT: C4.1, JP3.1 (A), U2.5 (OUT)
SEL: J1.6, JP2.2 (C), U1.4 (LR)
VIN: C3.1, J1.1, U2.1 (IN), U2.3 (EN)

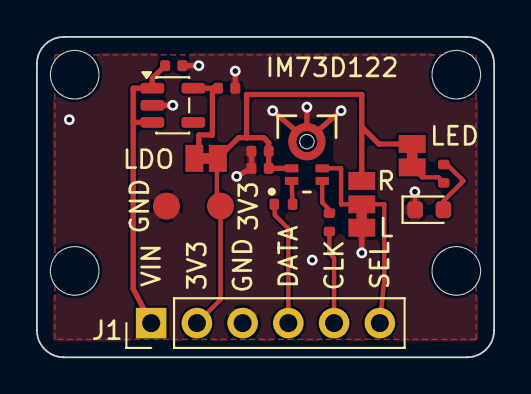
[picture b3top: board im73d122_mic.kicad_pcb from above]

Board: 4 copper layers, 25.4 x 17.8 mm, 20 parts (0 on the bottom side), 11 nets.
